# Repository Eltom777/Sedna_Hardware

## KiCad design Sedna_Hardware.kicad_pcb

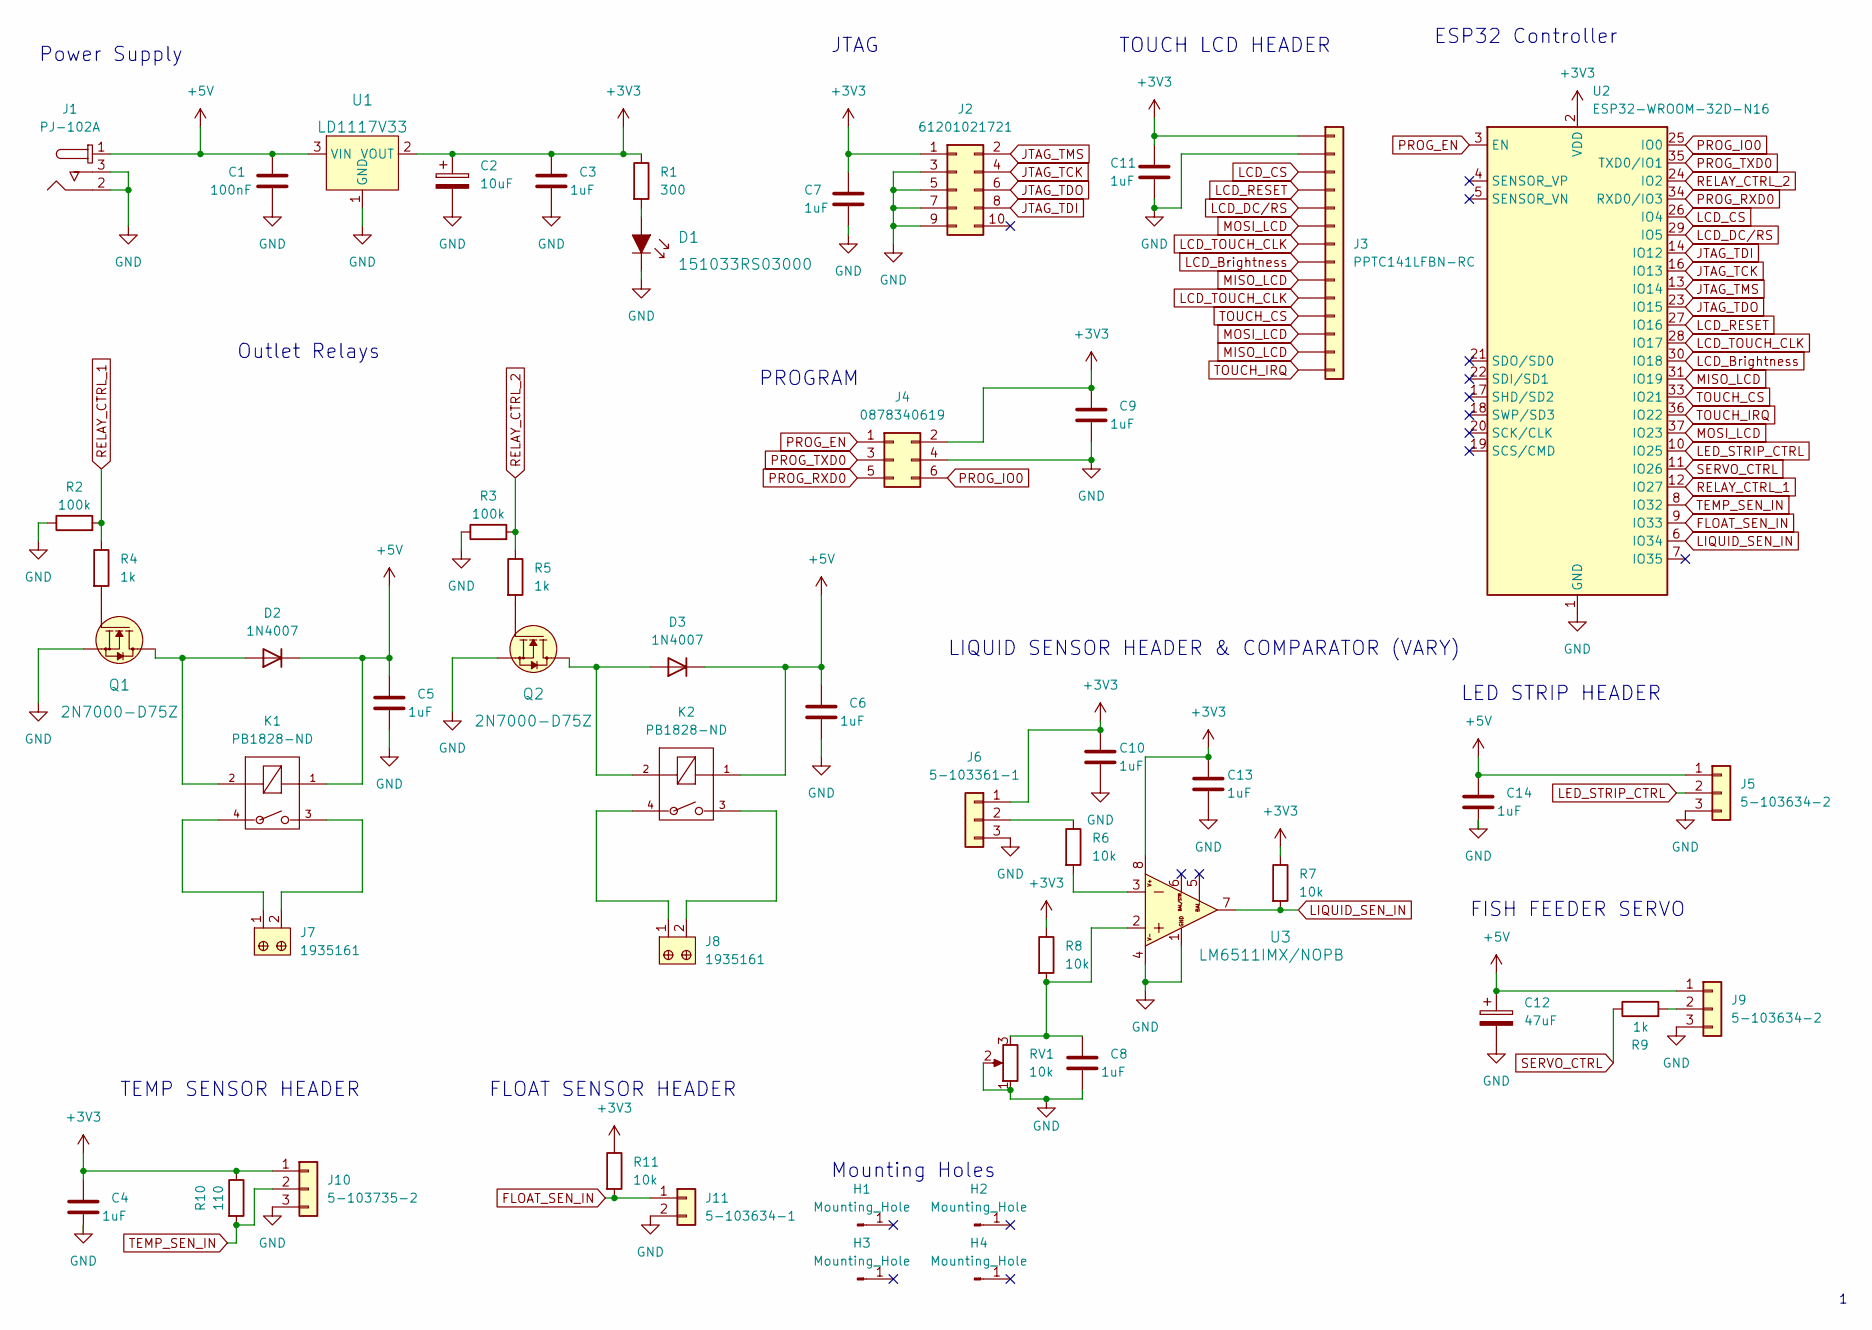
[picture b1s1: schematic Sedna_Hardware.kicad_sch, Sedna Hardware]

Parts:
C1: 100nF; C_Radial_D6.3mm_H5.0mm_P2.50mm; MPN K104K15X7RF53L2; Digi-Key_PN BC3324-ND
C2: 10uF; CP_Radial_D5.0mm_P2.50mm; MPN TAP106K016SCS; Digi-Key_PN 478-1839-ND
C3, C4, C5, C6, C7, C8, C9, C10, C11, C13, C14: 1uF; C_Axial_L3.8mm_D2.6mm_P7.50mm_Horizontal; MPN C410C105K3R5TA; Digi-Key_PN 399-C410C105K3R5TA-ND
C12: 47uF; CP_Radial_D5.0mm_P2.50mm; MPN UMT0G470MDD1TP; Digi-Key_PN 493-10267-1-ND
D1: 151033RS03000; LED_3mm_Radial; MPN 151033RS03000; Digi-Key_PN 732-5013-ND
D2, D3: 1N4007; D_DO-41_SOD81_P10.16mm_Horizontal; MPN 1N4007E-E3/54; Digi-Key_PN 1N4007E-E3/54GITR-ND
H1, H2, H3, H4: Mounting_Hole; MountingHole_3.5mm_Pad
J1: PJ-102A; Barrel_Jack_5.5mmODx2.1mmID_PJ-102A; MPN PJ-102A; Digi-Key_PN CP-102A-ND
J2: 61201021721; PinHeader_2x05_P2.54mm_Vertical; MPN 61201021721; Digi-Key_PN 732-2098-ND
J3: PPTC141LFBN-RC; PinHeader_1x14_P2.54mm_Vertical; MPN PPTC141LFBN-RC; Digi-Key_PN S7012-ND
J4: 0878340619; PinHeader_2x03_P2.54mm_Vertical; MPN 0878340619; Digi-Key_PN WM14718-ND
J5, J9: 5-103634-2; TE_5-103634-2; MPN 5-103634-2; Digi-Key_PN A33859-ND
J6: 5-103361-1; TE_5-103361-1; MPN 5-103361-1; Digi-Key_PN A35068-ND
J7, J8: 1935161; Terminal_Block_D1.3mm_P5mm; MPN 1935161; Digi-Key_PN 277-1667-ND
J10: 5-103735-2; MOLEX_1719740003; MPN 5-103735-2; Digi-Key_PN A33924-ND
J11: 5-103634-1; TE_2-103634-9; MPN 5-103634-1; Digi-Key_PN A33857-ND
K1, K2: PB1828-ND; TE_Connectivity-1461352-2-MFG; MPN PCH-105L2M,000; Digi-Key_PN PB1828-ND
Q1, Q2: 2N7000-D75Z; TO-92-3; MPN 2N7000-D75Z; Digi-Key_PN 2N7000-D75ZFSCT-ND
R1: 300; R_Axial_DIN0204_L3.6mm_D1.6mm_P5.08mm_Horizontal; MPN MBA02040C3000FRP00; Digi-Key_PN BC3491TR-ND
R2, R3: 100k; R_Axial_DIN0204_L3.6mm_D1.6mm_P5.08mm_Horizontal; MPN MBA02040C1003FCT00; Digi-Key_PN BC3240CT-ND
R4, R5, R9: 1k; R_Axial_DIN0204_L3.6mm_D1.6mm_P5.08mm_Horizontal; MPN MBA02040C1001FCT00; Digi-Key_PN BC3238CT-ND
R6, R7, R8, R11: 10k; R_Axial_DIN0204_L3.6mm_D1.6mm_P5.08mm_Horizontal; MPN MBA02040C1002FRP00; Digi-Key_PN BC10.0KXTR-ND
R10: 110; R_Axial_DIN0204_L3.6mm_D1.6mm_P5.08mm_Horizontal; MPN MBA02040C1100FC100; Digi-Key_PN 56-MBA02040C1100FC100CT-ND
RV1: 10k; TRIM_3306K-1-103; MPN 3306K-1-103; Digi-Key_PN 3306K-103-ND
U1: LD1117V33; TO-220-3_Horizontal_TabUp; MPN LD1117V33; Digi-Key_PN 497-1491-5-ND
U2: ESP32-WROOM-32D-N16; ESP32-WROOM-32; MPN ESP32-WROOM-32D-N16; Digi-Key_PN 1965-ESP32-WROOM-32D-N16TR-ND
U3: LM6511IMX/NOPB; SOIC-8_3.9x4.9mm_P1.27mm; MPN LM6511IM/NOPB; Digi-Key_PN LM6511IM/NOPB-ND

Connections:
+3V3: C2.1, C3.1, C4.1, C7.1, C9.1, C10.1, C11.1, C13.1, J2.1, J3.1, J4.2, J6.1, J10.1, R1.1, R7.1, R8.1, R10.1, R11.1, U1.2 (VOUT), U2.2 (VDD), U3.8
+5V: C1.1, C5.1, C6.1, C12.1, C14.1, D2.1 (K), D3.1 (K), J1.1, J5.1, J9.1, K1.1, K2.1, U1.3 (VIN)
FLOAT_SEN_IN: J11.1, R11.2, U2.9 (IO33)
GND: C1.2, C2.2, C3.2, C4.2, C5.2, C6.2, C7.2, C8.2, C9.2, C10.2, C11.2, C12.2, C13.2, C14.2, D1.2, J1.2, J1.3, J2.3, J2.5, J2.7, J2.9, J3.2, J4.4, J5.3, J6.3, J9.3, J10.3, J11.2, Q1.1 (S), Q2.1 (S), R2.1, R3.1, RV1.1, RV1.2, U1.1 (GND), U2.1 (GND), U2.15 (GND), U2.38 (GND), U2.39 (GND), U3.1, U3.4
JTAG_TCK: J2.4, U2.16 (IO13)
JTAG_TDI: J2.8, U2.14 (IO12)
JTAG_TDO: J2.6, U2.23 (IO15)
LCD_Brightness: J3.8, U2.30 (IO18)
LCD_CS: J3.3, U2.26 (IO4)
LCD_DC/RS: J3.5, U2.29 (IO5)
LCD_RESET: J3.4, U2.27 (IO16)
LCD_TOUCH_CLK: J3.7, J3.10, U2.28 (IO17)
LED_STRIP_CTRL: J5.2, U2.10 (IO25)
LIQUID_SEN_IN: R7.2, U2.6 (IO34), U3.7
MISO_LCD: J3.9, J3.13, U2.31 (IO19)
MOSI_LCD: J3.6, J3.12, U2.37 (IO23)
unnamed: C8.1, R8.2, RV1.3, U3.2
unnamed: D1.1, R1.2
unnamed: D2.2 (A), K1.2, Q1.3 (D)
unnamed: D3.2 (A), K2.2, Q2.3 (D)
unnamed: J6.2, R6.1
unnamed: J7.1, K1.4
unnamed: J7.2, K1.3
unnamed: J8.1, K2.4
unnamed: J8.2, K2.3
unnamed: J9.2, R9.2
unnamed: Q1.2 (G), R4.2
unnamed: Q2.2 (G), R5.2
unnamed: R6.2, U3.3
PROG_EN: J4.1, U2.3 (EN)
PROG_IO0: J4.6, U2.25 (IO0)
PROG_RXD0: J4.5, U2.34 (RXD0/IO3)
PROG_TXD0: J4.3, U2.35 (TXD0/IO1)
RELAY_CTRL_2: R3.2, R5.1, U2.24 (IO2)
SERVO_CTRL: R9.1, U2.11 (IO26)
TEMP_SEN_IN: J10.2, R10.2, U2.8 (IO32)
TOUCH_CS: J3.11, U2.33 (IO21)
TOUCH_IRQ: J3.14, U2.36 (IO22)

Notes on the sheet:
FISH FEEDER SERVO
PROGRAM
ESP32 Controller
LED STRIP HEADER
LIQUID SENSOR HEADER & COMPARATOR (VARY)
FLOAT SENSOR HEADER
Mounting Holes
TEMP SENSOR HEADER
TOUCH LCD HEADER
Power Supply
JTAG
Outlet Relays

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
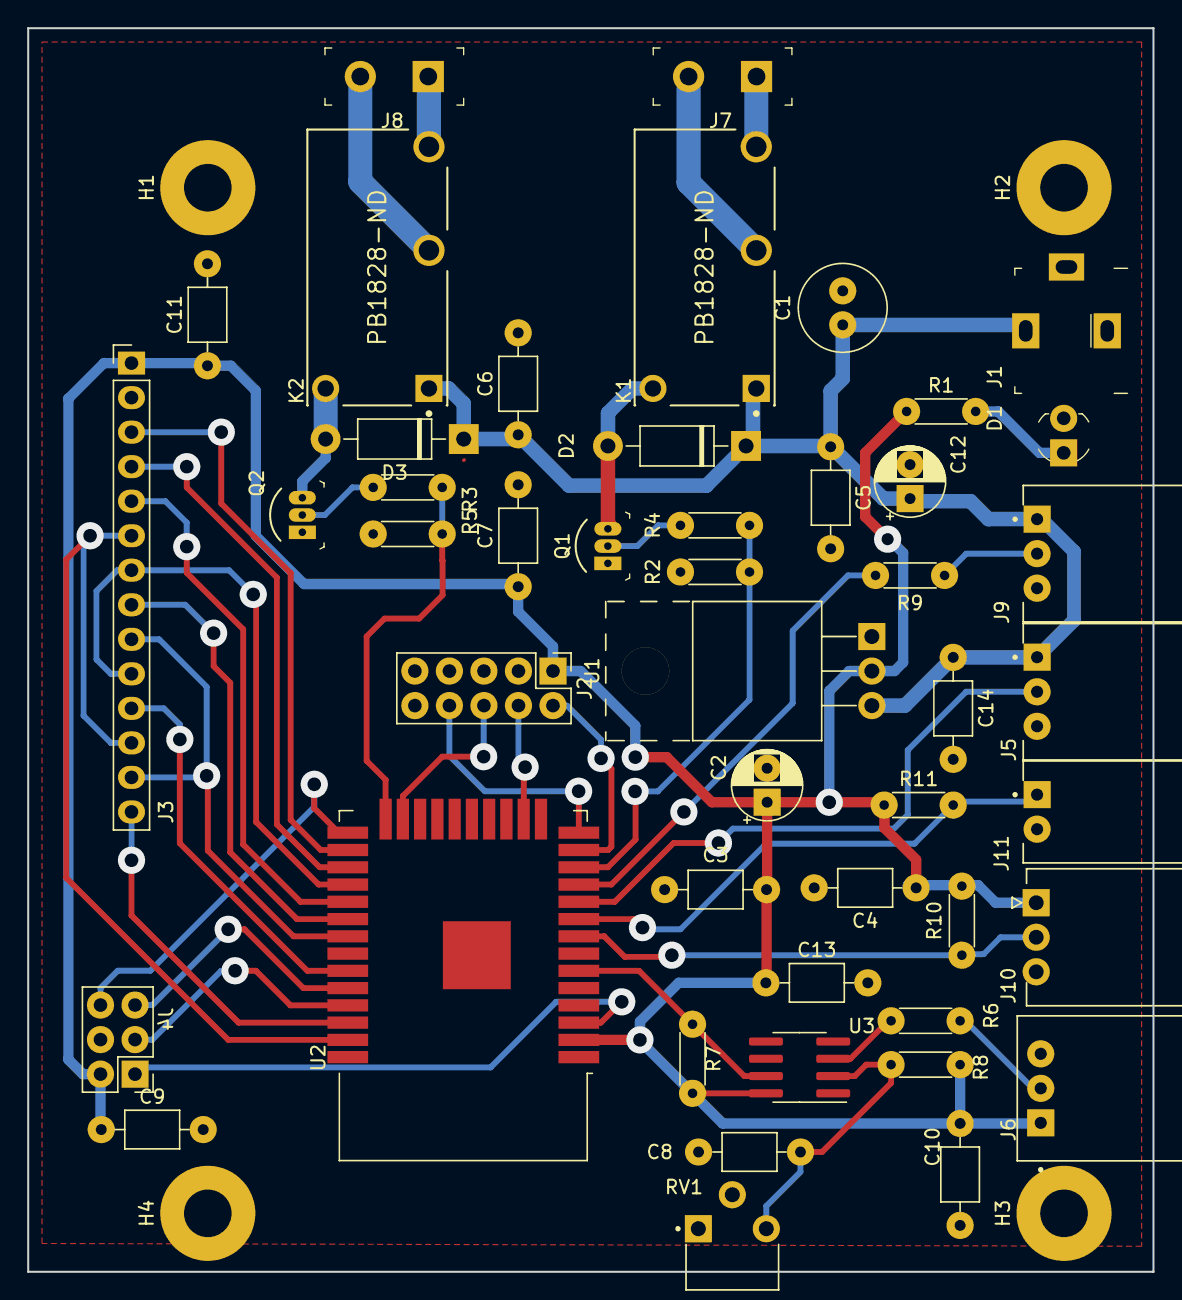
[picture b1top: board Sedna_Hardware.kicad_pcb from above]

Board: 2 copper layers, 82.8 x 91.5 mm, 51 parts (0 on the bottom side), 39 nets.

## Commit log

2022-02-15 init kicad project
2022-02-15 add 3rd kicad libs
2022-02-15 modified library path to 3rd libs
2022-02-16 Added various headers for sensors, servo, led strips, etc.
2022-02-20 add datasheets of components used
2022-02-20 started working on PCB
2022-02-20 Untangled rat net
2022-02-22 Replaced ESP32-WROOM-32E with ESP32-WROOM-32D. Stock issues
2022-02-28 Added footprints for shrouded headers
2022-02-28 Fixed schematic and pcb placement. added mounting holes
2022-02-28 fixed SPI connecion to LCD. Add correct screw terminals
2022-02-28 based PCB layout
2022-03-01 started layout tracks. Fixed regulator footprint
2022-03-01 adjusted track size of power bus
2022-03-02 finished track layout
2022-03-02 modified relay to correct footpring and symbol
2022-03-03 added LCD & box drawings
2022-03-03 Quick touch ups
2022-03-03 added resistor to servo. Placed most of tracks in bottom layer
2022-03-04 associated resistor and capacitor to DigiKey Procduct. Modified 1uf cap's footpring
2022-03-04 Modified potentimeter footprint
2022-03-04 cleaned up symbol properties of several components
2022-03-04 fixed symbol properties again
2022-03-04 modified relay due to stock issues
2022-03-04 updated connector properties
2022-03-04 placed new header's footpring
2022-03-14 placed potentiemeter and program header on the front side
2022-03-14 fixed silkscreen for some compoents
2022-03-18 Edit PCB making pads bigger
2022-03-18 flipped resistor and power terminal to front plane
2022-03-18 oopus forgot to flip power terminal to front plane
2022-03-18 edited via drill holes
2022-03-18 edited gbr files
2022-03-19 placed two tracks to LCD header and two pin header to back plane
2022-03-19 added gerber, drill and zip files to gitignore
2022-03-19 removed gerber, drile and zip files generated by Kicad
